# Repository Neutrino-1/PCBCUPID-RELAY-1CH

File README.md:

# GMOD-RELAY-1CH

This repo contains open source PCB files for PCBCUPID GMOD 1CH Relay Module <br/>
This particular PCB is designed using Kicad v9.0

**This design has been built and tested successfully!**
For more details, check out the product pages at

   * [Gmod-Relay-1CH](https://shop.pcbcupid.com/product/gm001/)
   * [Docs](https://learn.pcbcupid.com/boards/g-mod/relay-1-ch)
     
We are here to build India's largest open source hardware community, If you like to support
please consider buying the product from the above link!

[Creative Commons Attribution, Share-Alike license](https://creativecommons.org/licenses/by-sa/4.0/deed.en)
All text above must be included in any redistribution

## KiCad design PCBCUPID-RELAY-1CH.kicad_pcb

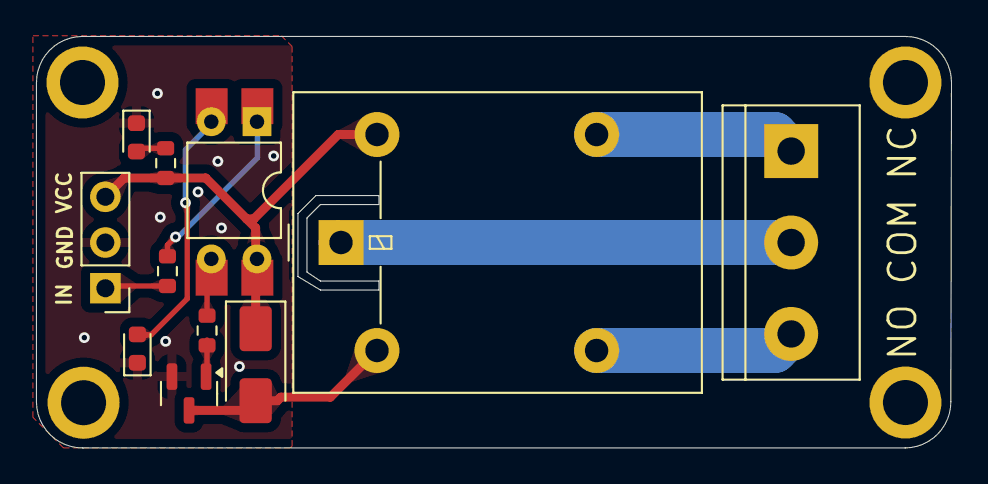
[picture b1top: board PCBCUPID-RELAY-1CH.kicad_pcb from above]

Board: 2 copper layers, 50.8 x 22.9 mm, 11 parts (0 on the bottom side), 9 nets.

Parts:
D1: SS34; D_SMA
D2: LED-R; LED_0603_1608Metric
D3: LED-B; LED_0603_1608Metric
J1: Output; TerminalBlock_bornier-3_P5.08mm
J3: Input; PinHeader_1x03_P2.54mm_Vertical
K1: Relay; Relay_SPDT_Omron-G5LE-1
Q2: MMBT3904; SOT-23
R1: 330R; R_0603_1608Metric
R2: 1K; R_0603_1608Metric
R3: 220R; R_0603_1608Metric
U1: EL817; SMDIP-4_W9.53mm

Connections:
/COM: J1.2, K1.1
/IN: J3.1, R1.1
/NC: J1.1, K1.4
/NO: J1.3, K1.3
GND: D2.1 (K), D3.1 (K), J3.2, Q2.2 (E)
unnamed: D1.2 (A), K1.2, Q2.3 (C)
unnamed: D3.2 (A), R3.1
unnamed: Q2.1 (B), R2.2
VCC: D1.1 (K), J3.3, K1.5, R3.2

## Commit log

2025-06-28 Initial Upload
2025-07-04 Version 1.0 - Uploaded the correct files
